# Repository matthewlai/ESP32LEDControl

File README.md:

# ESP32LEDControl

ESP32-based LED controller for WS2812B-compatible LEDs, powered by USB Type-C.

This is the hardware component of Fede Heinz's [Blinkenlights project](https://github.com/fheinz/Blinkenlights).

See [this blog post](https://dubiouscreations.com/2021/05/04/designing-an-esp32-based-rgb-matrix-driver-and-making-500-of-them/) for more details.

This hardware design is licensed under Attribution-ShareAlike 4.0 International (CC BY-SA 4.0) as published by the Creative Commons. You can find a copy of the license [here](https://creativecommons.org/licenses/by-sa/4.0/).

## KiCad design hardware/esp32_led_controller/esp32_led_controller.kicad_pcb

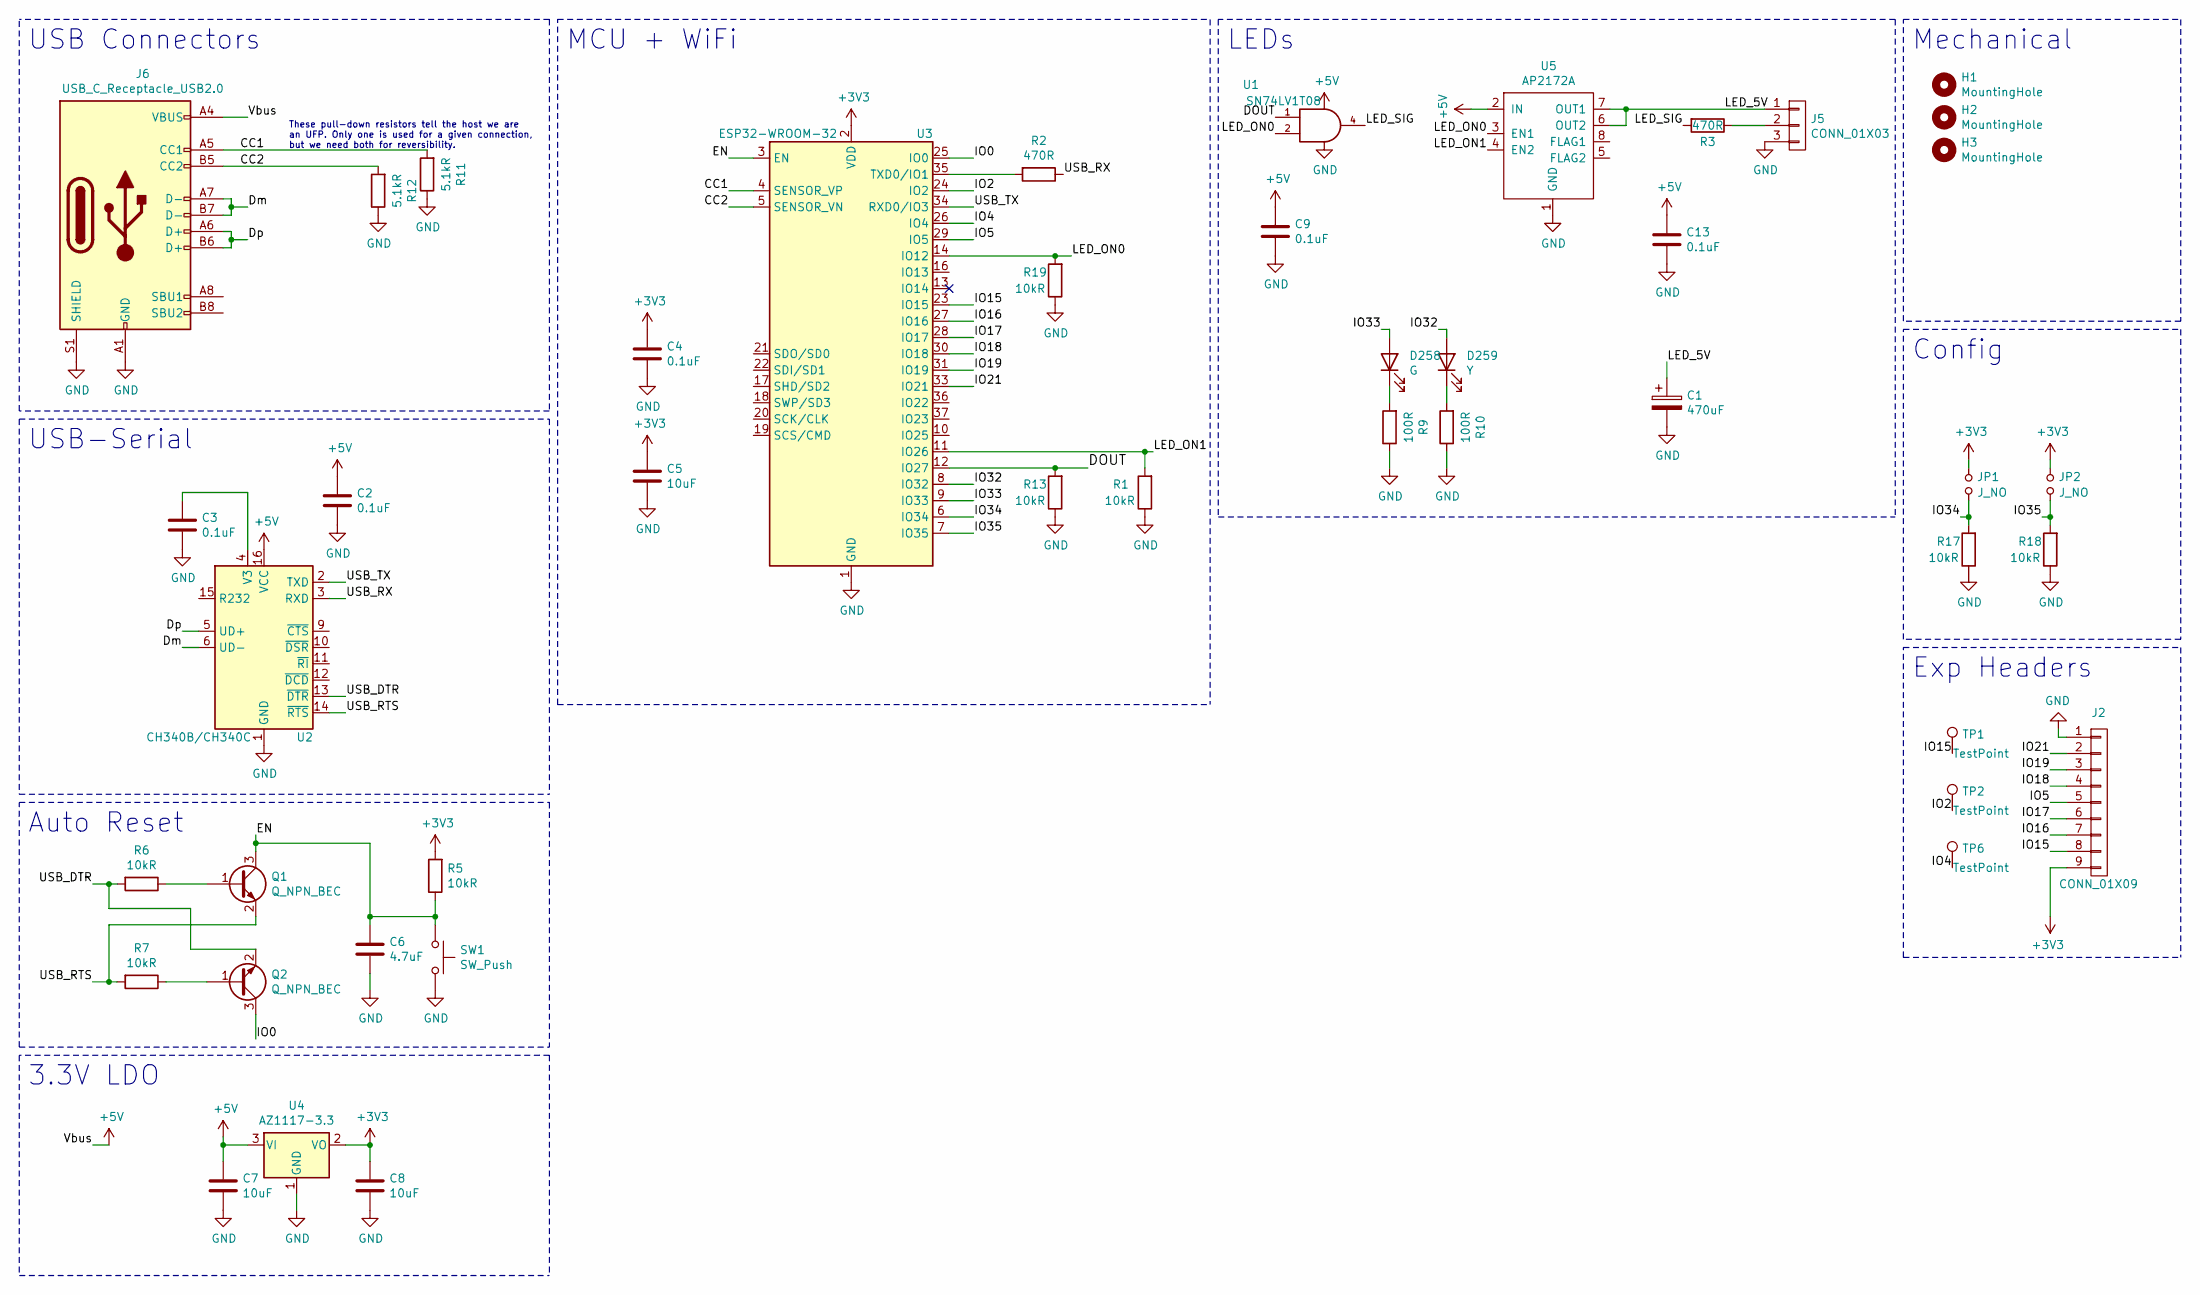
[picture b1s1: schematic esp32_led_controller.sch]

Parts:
C1: 470uF; CP_Radial_D5.0mm_P2.00mm; LCSC C112519
C2, C3, C4, C9, C13: 0.1uF; C_0402_1005Metric; LCSC C1525
C5, C7, C8: 10uF; C_0402_1005Metric; LCSC C15525
C6: 4.7uF; C_0402_1005Metric; LCSC C23733
D258: G; LED_0603_1608Metric; LCSC C72043
D259: Y; LED_0603_1608Metric; LCSC C72038
H1, H2, H3: MountingHole; MountingHole_2.2mm_M2
J2: CONN_01X09; PinHeader_1x09_P2.54mm_Vertical
J5: CONN_01X03; KF128L-3.81-3P; LCSC C474933
J6: USB_C_Receptacle_USB2.0; USB_C_Receptacle_HRO_TYPE-C-31-M-12; LCSC C165948
JP1, JP2: J_NO; SolderJumper-2_P1.3mm_Open_TrianglePad1.0x1.5mm
Q1, Q2: Q_NPN_BEC; SOT-23; LCSC C2150
R1, R5, R6, R7, R13, R17, R18, R19: 10kR; R_0402_1005Metric; LCSC C25744
R2, R3: 470R; R_0402_1005Metric; LCSC C25117
R9, R10: 100R; R_0402_1005Metric; LCSC C25076
R11, R12: 5.1kR; R_0402_1005Metric; LCSC C25905
SW1: SW_Push; SW_Push_1P1T_NO_5.1x5.1mm; LCSC C318887
TP1, TP2, TP6: TestPoint; TestPoint_Pad_4.0x4.0mm
U1: SN74LV1T08; SOT-353_SC-70-5; LCSC C130199
U2: CH340B/CH340C; SOIC-16_3.9x9.9mm_P1.27mm; LCSC C81010
U3: ESP32-WROOM-32; LCSC C82899
U4: AZ1117-3.3; SOT-89-3; LCSC C108493
U5: AP2172A; SO-8_3.9x4.9mm_P1.27mm; LCSC C151327

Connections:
+3V3: C4.1, C5.1, C8.1, J2.9, JP1.1, JP2.1, R5.2, U3.2 (VDD), U4.2 (VO)
+5V: C2.1, C7.1, C9.1, C13.1, J6.A4 (VBUS), J6.A9 (VBUS), J6.B4 (VBUS), J6.B9 (VBUS), U1.5 (VCC), U2.16 (VCC), U4.3 (VI), U5.2 (IN)
/CC1: J6.A5 (CC1), R11.2, U3.4 (SENSOR_VP)
/CC2: J6.B5 (CC2), R12.2, U3.5 (SENSOR_VN)
/DOUT: R13.2, U1.1, U3.12 (IO27)
/Dm: J6.A7 (D-), J6.B7 (D-), U2.6 (UD-)
/Dp: J6.A6 (D+), J6.B6 (D+), U2.5 (UD+)
/EN: C6.1, Q1.3 (C), R5.1, SW1.1, U3.3 (EN)
/IO0: Q2.3 (C), U3.25 (IO0)
/IO2: TP2.1, U3.24 (IO2)
/IO4: TP6.1, U3.26 (IO4)
/IO5: J2.5, U3.29 (IO5)
/IO15: J2.8, TP1.1, U3.23 (IO15)
/IO16: J2.7, U3.27 (IO16)
/IO17: J2.6, U3.28 (IO17)
/IO18: J2.4, U3.30 (IO18)
/IO19: J2.3, U3.31 (IO19)
/IO21: J2.2, U3.33 (IO21)
/IO32: D259.2 (A), U3.8 (IO32)
/IO33: D258.2 (A), U3.9 (IO33)
/IO34: JP1.2, R17.2, U3.6 (IO34)
/IO35: JP2.2, R18.2, U3.7 (IO35)
/LED_5V: C1.1, J5.1, U5.6 (OUT2), U5.7 (OUT1)
/LED_ON0: R19.2, U1.2, U3.14 (IO12), U5.3 (EN1)
/LED_ON1: R1.2, U3.11 (IO26), U5.4 (EN2)
/LED_SIG: R3.2, U1.4
/USB_DTR: Q2.2 (E), R6.2, U2.13 (~DTR)
/USB_RTS: Q1.2 (E), R7.2, U2.14 (~RTS)
/USB_RX: R2.1, U2.3 (RXD)
/USB_TX: U2.2 (TXD), U3.34 (RXD0/IO3)
GND: C1.2, C2.2, C3.2, C4.2, C5.2, C6.2, C7.2, C8.2, C9.2, C13.2, J2.1, J5.3, J6.A1 (GND), J6.A12 (GND), J6.B1 (GND), J6.B12 (GND), J6.S1 (SHIELD), R1.1, R9.1, R10.1, R11.1, R12.1, R13.1, R17.1, R18.1, R19.1, SW1.2, U1.3 (GND), U2.1 (GND), U3.1 (GND), U3.15 (GND), U3.38 (GND), U3.39 (GND), U4.1 (GND), U5.1 (GND)
unnamed: C3.1, U2.4 (V3)
unnamed: D258.1 (K), R9.2
unnamed: D259.1 (K), R10.2
unnamed: J5.2, R3.1
unnamed: Q1.1 (B), R6.1
unnamed: Q2.1 (B), R7.1
unnamed: R2.2, U3.35 (TXD0/IO1)

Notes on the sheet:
USB-Serial
Auto Reset
MCU + WiFi
3.3V LDO
Exp Headers
LEDs
Mechanical
USB Connectors
These pull-down resistors tell the host we are an UFP. Only one is used for a given connection, but we need both for reversibility.
Config

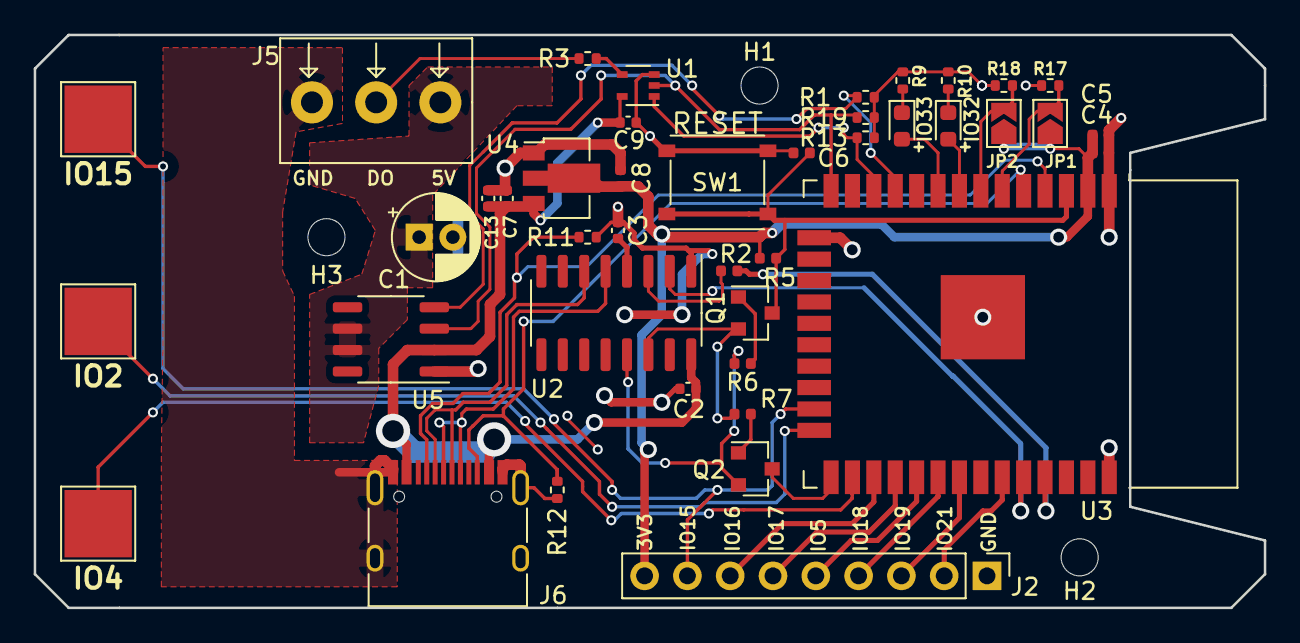
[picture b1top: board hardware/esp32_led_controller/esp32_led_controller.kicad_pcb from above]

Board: 4 copper layers, 73.0 x 34.0 mm, 45 parts (0 on the bottom side), 38 nets.

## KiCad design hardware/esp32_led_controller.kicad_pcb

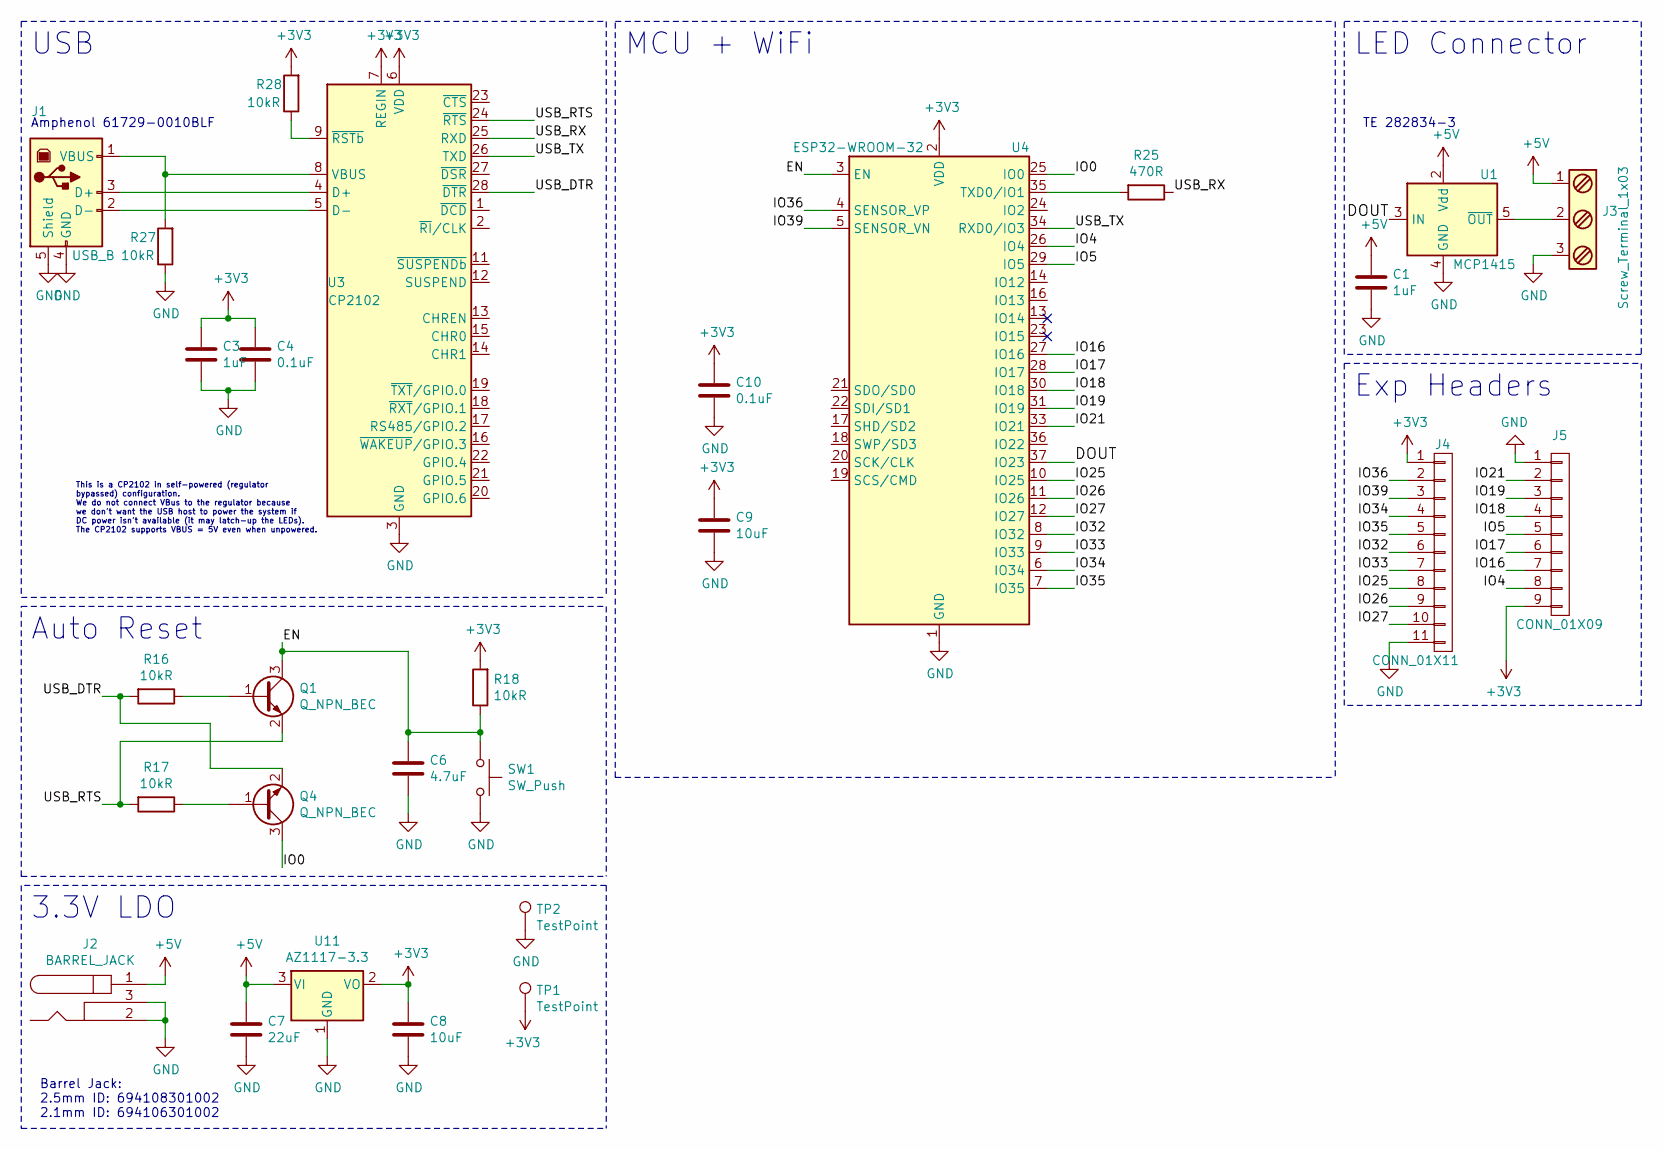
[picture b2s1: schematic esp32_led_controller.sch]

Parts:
C1, C3: 1uF; C_0402_1005Metric; LCSC C52923
C4, C10: 0.1uF; C_0402_1005Metric; LCSC C1525
C6: 4.7uF; C_0402_1005Metric; LCSC C23733
C7: 22uF; C_0805_2012Metric; LCSC C45783
C8, C9: 10uF; C_0402_1005Metric; LCSC C15525
J1: USB_B; Amphenol_61729_0010BLF
J2: BARREL_JACK; BarrelJack_Wuerth_6941xx301002
J3: Screw_Terminal_1x03; TerminalBlock_TE_282834-3_1x03_P2.54mm_Horizontal
J4: CONN_01X11; PinHeader_1x11_P2.54mm_Vertical
J5: CONN_01X09; PinHeader_1x09_P2.54mm_Vertical
Q1, Q4: Q_NPN_BEC; SOT-23; LCSC C2150
R16, R17, R18, R27, R28: 10kR; R_0402_1005Metric; LCSC C25744
R25: 470R; R_0402_1005Metric; LCSC C25117
SW1: SW_Push; SW_Push_1P1T_NO_5.1x5.1mm; LCSC C318887
TP1, TP2: TestPoint; TestPoint_Loop_D3.50mm_Drill1.4mm_Beaded
U1: MCP1415; SOT-23-5; LCSC C83776
U3: CP2102; QFN-28-1EP_5x5mm_P0.5mm_EP3.35x3.35mm; LCSC C6568
U4: ESP32-WROOM-32; LCSC C82899
U11: AZ1117-3.3; SOT-223-3_TabPin2; LCSC C92102

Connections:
+3V3: C3.1, C4.1, C8.1, C9.1, C10.1, J4.1, J5.9, R18.2, R28.2, TP1.1, U3.6 (VDD), U3.7 (REGIN), U4.2 (VDD), U11.2 (VO)
+5V: C1.1, C7.1, J2.1, J3.1, U1.2 (Vdd), U11.3 (VI)
/DOUT: U1.3 (IN), U4.37 (IO23)
/EN: C6.1, Q1.3 (C), R18.1, SW1.1, U4.3 (EN)
/IO0: Q4.3 (C), U4.25 (IO0)
/IO4: J5.8, U4.26 (IO4)
/IO5: J5.5, U4.29 (IO5)
/IO16: J5.7, U4.27 (IO16)
/IO17: J5.6, U4.28 (IO17)
/IO18: J5.4, U4.30 (IO18)
/IO19: J5.3, U4.31 (IO19)
/IO21: J5.2, U4.33 (IO21)
/IO25: J4.8, U4.10 (IO25)
/IO26: J4.9, U4.11 (IO26)
/IO27: J4.10, U4.12 (IO27)
/IO32: J4.6, U4.8 (IO32)
/IO33: J4.7, U4.9 (IO33)
/IO34: J4.4, U4.6 (IO34)
/IO35: J4.5, U4.7 (IO35)
/IO36: J4.2, U4.4 (SENSOR_VP)
/IO39: J4.3, U4.5 (SENSOR_VN)
/USB_DTR: Q4.2 (E), R16.2, U3.28 (~DTR)
/USB_RTS: Q1.2 (E), R17.2, U3.24 (~RTS)
/USB_RX: R25.1, U3.25 (RXD)
/USB_TX: U3.26 (TXD), U4.34 (RXD0/IO3)
GND: C1.2, C3.2, C4.2, C6.2, C7.2, C8.2, C9.2, C10.2, J1.4 (GND), J1.5 (Shield), J2.2, J2.3, J3.3, J4.11, J5.1, R27.1, SW1.2, TP2.1, U1.4 (GND), U3.3 (GND), U3.29 (GND), U4.1 (GND), U4.15 (GND), U4.38 (GND), U4.39 (GND), U11.1 (GND)
unnamed: J1.1 (VBUS), R27.2, U3.8 (VBUS)
unnamed: J1.2 (D-), U3.5 (D-)
unnamed: J1.3 (D+), U3.4 (D+)
unnamed: J3.2, U1.5 (~OUT)
unnamed: Q1.1 (B), R16.1
unnamed: Q4.1 (B), R17.1
unnamed: R25.2, U4.35 (TXD0/IO1)
unnamed: R28.1, U3.9 (~RSTb)

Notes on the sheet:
USB
Auto Reset
MCU + WiFi
3.3V LDO
LED Connector
This is a CP2102 in self-powered (regulator bypassed) configuration. We do not connect VBus to the regulator because we don't want the USB host to power the system if DC power isn't available (it may latch-up the LEDs). The CP2102 supports VBUS = 5V even when unpowered.
Barrel Jack: 2.5mm ID: 694108301002 2.1mm ID: 694106301002
Amphenol 61729-0010BLF
TE 282834-3
Exp Headers

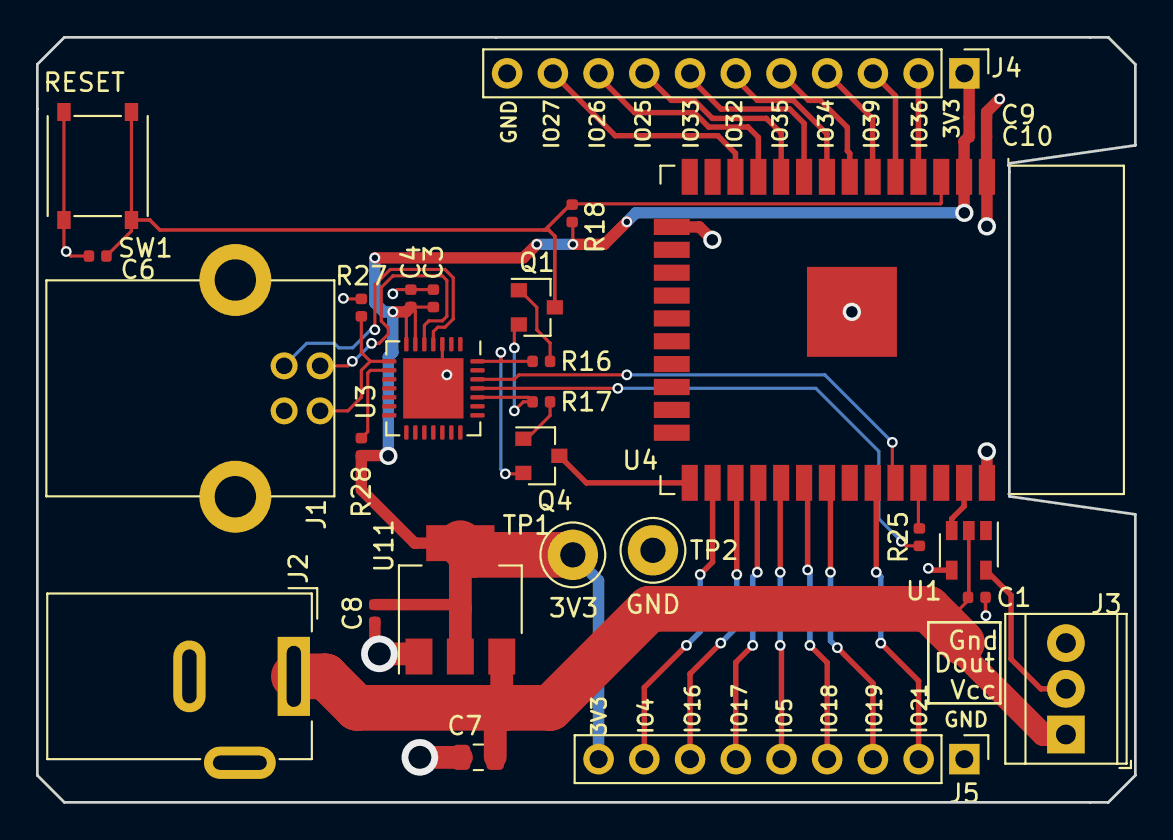
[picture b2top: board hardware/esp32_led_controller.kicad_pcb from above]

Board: 4 copper layers, 61.0 x 42.5 mm, 28 parts (0 on the bottom side), 34 nets.

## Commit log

2021-02-07 Finished design with integrated LED matrix
2021-02-07 Directory move
2021-02-09 Improved silkscreen and added test points
2021-02-09 Added configuration jumpers
2021-02-09 Updated BOM
2021-02-09 Added missing annotations
2021-05-02 Added scope shots for rev4 boards
2021-05-02 Added rev4 hardware design
2021-05-02 Added panelization instructions and results
2021-05-04 Updated schematics aesthetics, and added board photo
2021-05-04 Removed panelisation outputs
2021-05-04 docs re-org
2021-05-04 Added rev4 hardware test sketch
